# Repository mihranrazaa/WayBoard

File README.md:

# WayBoard
A Keyboard Design for ME and YOU

## Overview
a 60% keyboard design With very minimal design, it is based on RP2040 plus with a type C port which came in-built with the MCU, there total of 61 MX switches design with 5 Stabilizer type switches. A small minimal keyboard :).

## Bit in depth info
The keyboard is designed to be sleek and plane it has RP2040 plus as the MCU and Cherry MX Brown Switches for the keys which are used for versatile purposes (that's what i saw at least). The main firmware is KMK based and the Firmware has already been released, you can find that in the Firmware and Production folder, I hate using different cables so having type c inbuilt in the RP2040 plus is a win-win. I added A small space in the bottom right of the keyboard which will act as a handle kind of things and also look good

---

## Images

**THE ABOVE IMAGES ARE THE LATEST ITERATION OF CAD**

---

## Files to build 

### PCB 

The files for the PCB and Schematics are available in the PCB folder and gerber files are added in the Production folder..

### 3D Case (CAD)

The step files for the keyboard are available in the CAD folder and also in the Production Folder.

Can't add a combine image of pcb with components my laptop can't handle all that together..
Other than this you just have to purchase the Components given below and assemble them.

---

## BOM

| Component                 | Quantity | Note                                                                                    | Price    | Link                                                                                                                                       |
| ------------------------- | -------- | --------------------------------------------------------------------------------------- | -------- | ------------------------------------------------------------------------------------------------------------------------------------------ |
| Cherry MX Switches(Brown) | 1       | Couldn't find a proper retailer on Amazon.They are selling for the right amount i think, | 32USD    | [Available](https://www.keychron.com/products/cherry-switch-set?variant=39298816835673)                                                    |
| White Keycaps set         | 1        | Good Asthetics are important I will keep the body grey :)                               | 25USD    | [Available](https://www.keychron.com/products/cherry-profile-double-shot-pbt-full-set-keycaps-dolch-red-gray-white-mint-blue-black-yellow) |
| Stabilizer set            | 1        | It has 2 extra Stabilizers just in case..                                               | 20USD    | [Available](https://amzn.in/d/dM157FJ) [Available](https://amzn.in/d/5Nto8PQ)                                                              |
| Case & PCB                | 1        | I will make them through any local business                                             | 15-20USD |                                                                                                                                            |
| TOTAL                     |          |                                                                                         | 100USD   |                                                                                                                                            |

Other than this you also need M3 srews but i didn't included them as i already have them..

---

## Extra Stuff

### Gratitude
- Thanks to Hackclub and Hackpad for making me do this brilliant project, More coming :).
- Thanks to my potato for helping me till the end.
- Thanks to myself for completing the project and not getting distracted with another project.
- And Thank you for Reading?

### Challanging
- The only challanging part was designing the PCB and Schematics, first i was overthinking for what MCU should i choose then i took some time on footprints and symbols..
- CAD is TUFF!
---

## End
Check my [BLOG](https://mihranrazaa.pages.dev/)
~ mihranrazaa

BYEEE

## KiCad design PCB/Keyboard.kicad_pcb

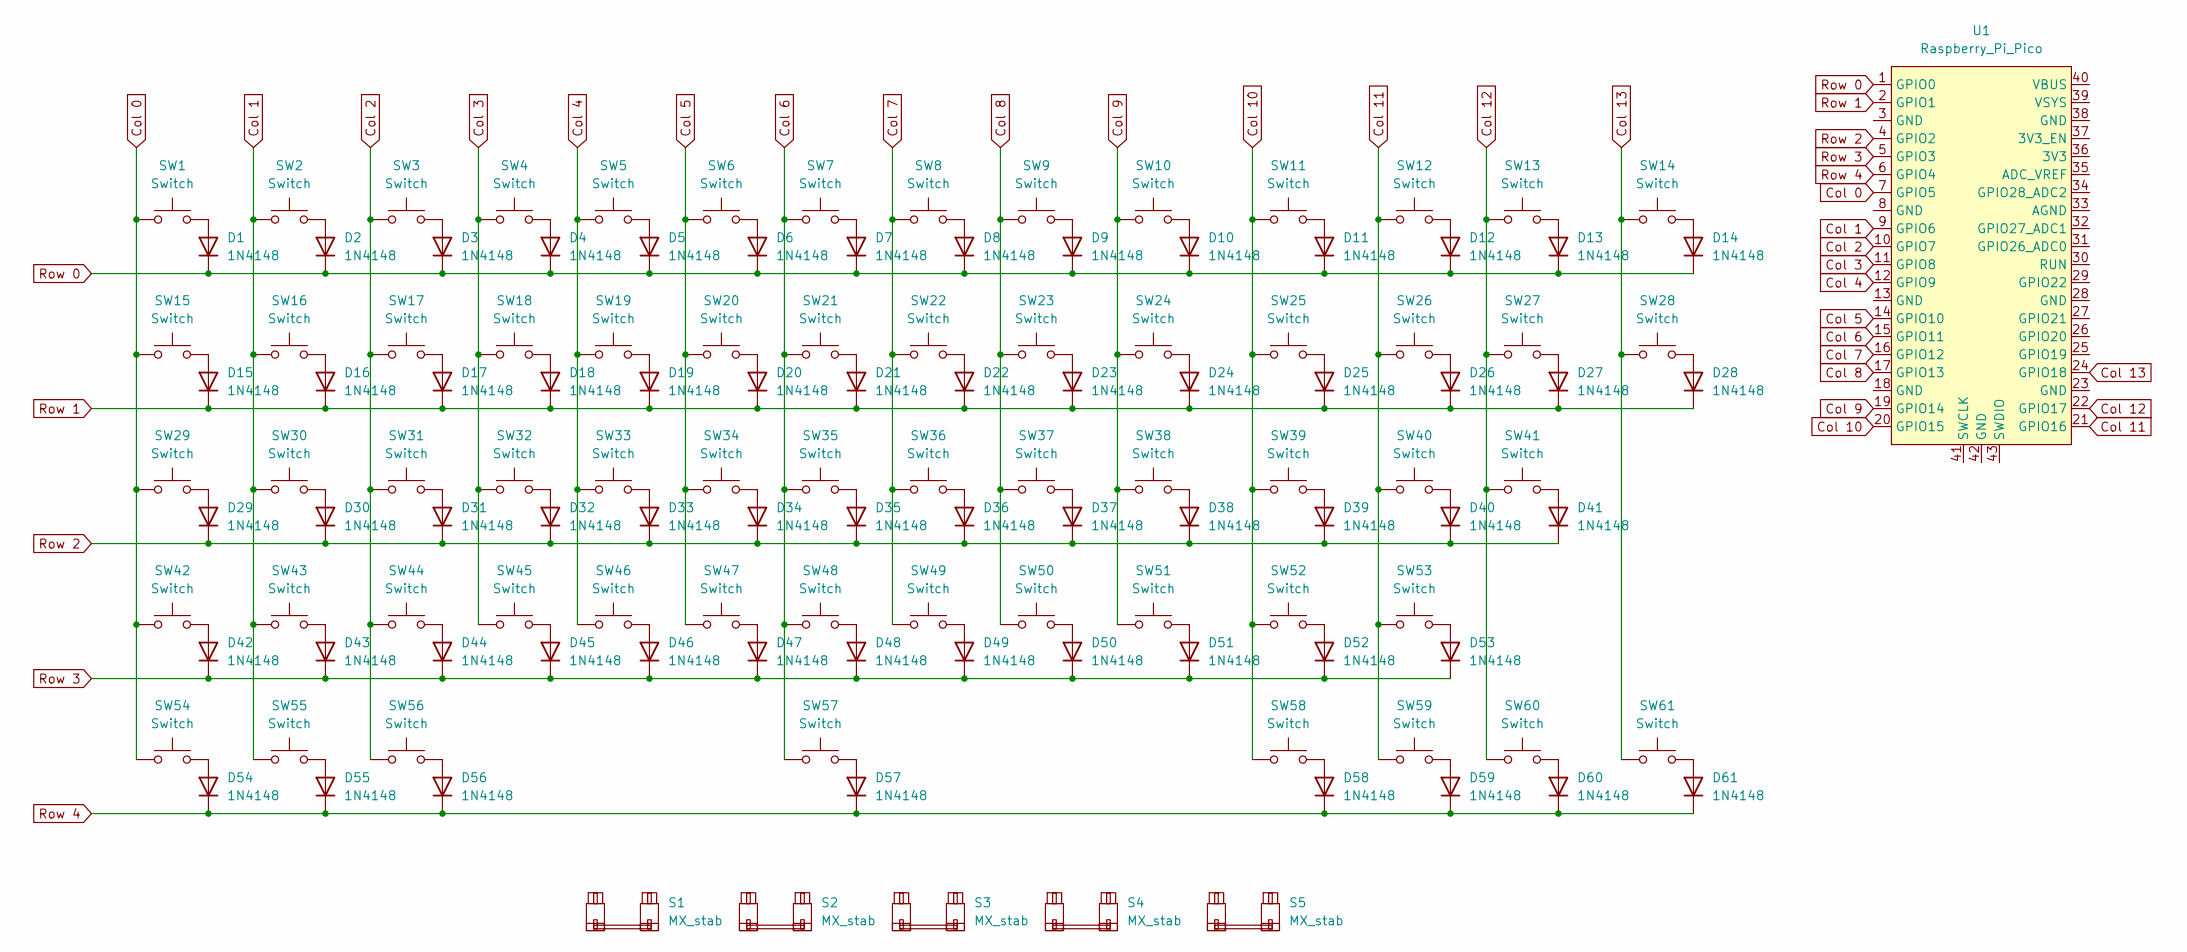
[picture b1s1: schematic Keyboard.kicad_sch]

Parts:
D1, D2, D3, D4, D5, D6, D7, D8, D9, D10, D11, D12, D13, D14, D15, D16, D17, D18, D19, D20, D21, D22, D23, D24, D25, D26, D27, D28, D29, D30, D31, D32, D33, D34, D35, D36, D37, D38, D39, D40, D41, D42, D43, D44, D45, D46, D47, D48, D49, D50, D51, D52, D53, D54, D55, D56, D57, D58, D59, D60, D61: 1N4148; D_DO-35_SOD27_P7.62mm_Horizontal
S1: MX_stab; STAB_MX_P_6.25u
S2: MX_stab; STAB_MX_P_2u
S3, S4: MX_stab; STAB_MX_P_2.25u
S5: MX_stab; STAB_MX_P_2.75u
SW1, SW2, SW3, SW4, SW5, SW6, SW7, SW8, SW9, SW10, SW11, SW12, SW13, SW14, SW16, SW17, SW18, SW19, SW20, SW21, SW22, SW23, SW24, SW25, SW26, SW27, SW30, SW31, SW32, SW33, SW34, SW35, SW36, SW37, SW38, SW39, SW40, SW41, SW42, SW43, SW44, SW45, SW46, SW47, SW48, SW49, SW50, SW51, SW52, SW53, SW57: Switch; SW_MX_1u
SW15, SW28: Switch; SW_MX_1.5u
SW29: Switch; SW_MX_1.75u
SW54, SW55, SW56, SW58, SW59, SW60, SW61: Switch; SW_MX_1.25u
U1: Raspberry_Pi_Pico

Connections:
Col 0: SW1.1, SW15.1, SW29.1, SW42.1, SW54.1, U1.7 (GPIO5)
Col 1: SW2.1, SW16.1, SW30.1, SW43.1, SW55.1, U1.9 (GPIO6)
Col 2: SW3.1, SW17.1, SW31.1, SW44.1, SW56.1, U1.10 (GPIO7)
Col 3: SW4.1, SW18.1, SW32.1, SW45.1, U1.11 (GPIO8)
Col 4: SW5.1, SW19.1, SW33.1, SW46.1, U1.12 (GPIO9)
Col 5: SW6.1, SW20.1, SW34.1, SW47.1, U1.14 (GPIO10)
Col 6: SW7.1, SW21.1, SW35.1, SW48.1, SW57.1, U1.15 (GPIO11)
Col 7: SW8.1, SW22.1, SW36.1, SW49.1, U1.16 (GPIO12)
Col 8: SW9.1, SW23.1, SW37.1, SW50.1, U1.17 (GPIO13)
Col 9: SW10.1, SW24.1, SW38.1, SW51.1, U1.19 (GPIO14)
Col 10: SW11.1, SW25.1, SW39.1, SW52.1, SW58.1, U1.20 (GPIO15)
Col 11: SW12.1, SW26.1, SW40.1, SW53.1, SW59.1, U1.21 (GPIO16)
Col 12: SW13.1, SW27.1, SW41.1, SW60.1, U1.22 (GPIO17)
Col 13: SW14.1, SW28.1, SW61.1, U1.24 (GPIO18)
unnamed: D1.2 (A), SW1.2
unnamed: D2.2 (A), SW2.2
unnamed: D3.2 (A), SW3.2
unnamed: D4.2 (A), SW4.2
unnamed: D5.2 (A), SW5.2
unnamed: D6.2 (A), SW6.2
unnamed: D7.2 (A), SW7.2
unnamed: D8.2 (A), SW8.2
unnamed: D9.2 (A), SW9.2
unnamed: D10.2 (A), SW10.2
unnamed: D11.2 (A), SW11.2
unnamed: D12.2 (A), SW12.2
unnamed: D13.2 (A), SW13.2
unnamed: D14.2 (A), SW14.2
unnamed: D15.2 (A), SW15.2
unnamed: D16.2 (A), SW16.2
unnamed: D17.2 (A), SW17.2
unnamed: D18.2 (A), SW18.2
unnamed: D19.2 (A), SW19.2
unnamed: D20.2 (A), SW20.2
unnamed: D21.2 (A), SW21.2
unnamed: D22.2 (A), SW22.2
unnamed: D23.2 (A), SW23.2
unnamed: D24.2 (A), SW24.2
unnamed: D25.2 (A), SW25.2
unnamed: D26.2 (A), SW26.2
unnamed: D27.2 (A), SW27.2
unnamed: D28.2 (A), SW28.2
unnamed: D29.2 (A), SW29.2
unnamed: D30.2 (A), SW30.2
unnamed: D31.2 (A), SW31.2
unnamed: D32.2 (A), SW32.2
unnamed: D33.2 (A), SW33.2
unnamed: D34.2 (A), SW34.2
unnamed: D35.2 (A), SW35.2
unnamed: D36.2 (A), SW36.2
unnamed: D37.2 (A), SW37.2
unnamed: D38.2 (A), SW38.2
unnamed: D39.2 (A), SW39.2
unnamed: D40.2 (A), SW40.2
unnamed: D41.2 (A), SW41.2
unnamed: D42.2 (A), SW42.2
unnamed: D43.2 (A), SW43.2
unnamed: D44.2 (A), SW44.2
unnamed: D45.2 (A), SW45.2
unnamed: D46.2 (A), SW46.2
unnamed: D47.2 (A), SW47.2
unnamed: D48.2 (A), SW48.2
unnamed: D49.2 (A), SW49.2
unnamed: D50.2 (A), SW50.2
unnamed: D51.2 (A), SW51.2
unnamed: D52.2 (A), SW52.2
unnamed: D53.2 (A), SW53.2
unnamed: D54.2 (A), SW54.2
unnamed: D55.2 (A), SW55.2
unnamed: D56.2 (A), SW56.2
unnamed: D57.2 (A), SW57.2
unnamed: D58.2 (A), SW58.2
unnamed: D59.2 (A), SW59.2
unnamed: D60.2 (A), SW60.2
unnamed: D61.2 (A), SW61.2
Row 0: D1.1 (K), D2.1 (K), D3.1 (K), D4.1 (K), D5.1 (K), D6.1 (K), D7.1 (K), D8.1 (K), D9.1 (K), D10.1 (K), D11.1 (K), D12.1 (K), D13.1 (K), D14.1 (K), U1.1 (GPIO0)
Row 1: D15.1 (K), D16.1 (K), D17.1 (K), D18.1 (K), D19.1 (K), D20.1 (K), D21.1 (K), D22.1 (K), D23.1 (K), D24.1 (K), D25.1 (K), D26.1 (K), D27.1 (K), D28.1 (K), U1.2 (GPIO1)
Row 2: D29.1 (K), D30.1 (K), D31.1 (K), D32.1 (K), D33.1 (K), D34.1 (K), D35.1 (K), D36.1 (K), D37.1 (K), D38.1 (K), D39.1 (K), D40.1 (K), D41.1 (K), U1.4 (GPIO2)
Row 3: D42.1 (K), D43.1 (K), D44.1 (K), D45.1 (K), D46.1 (K), D47.1 (K), D48.1 (K), D49.1 (K), D50.1 (K), D51.1 (K), D52.1 (K), D53.1 (K), U1.5 (GPIO3)
Row 4: D54.1 (K), D55.1 (K), D56.1 (K), D57.1 (K), D58.1 (K), D59.1 (K), D60.1 (K), D61.1 (K), U1.6 (GPIO4)

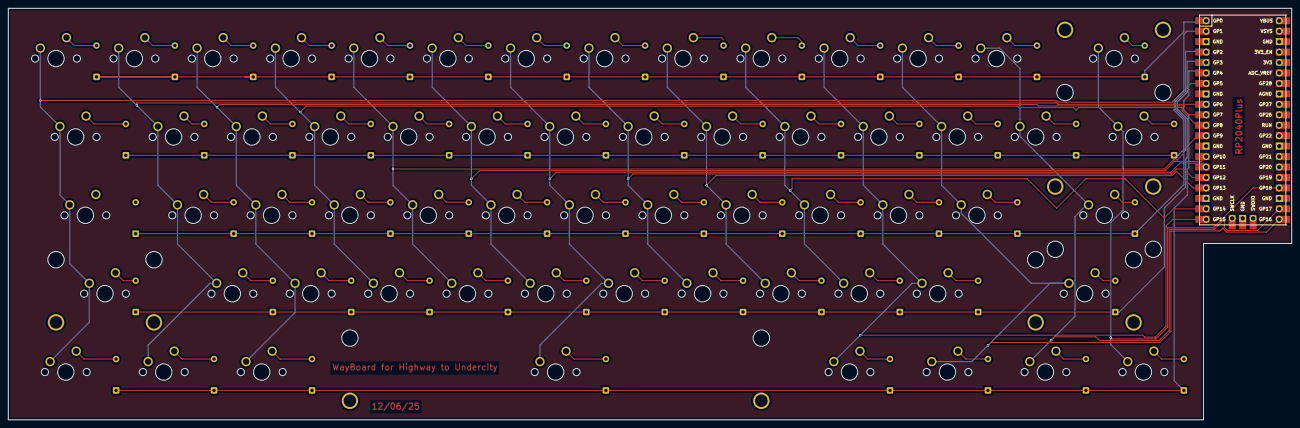
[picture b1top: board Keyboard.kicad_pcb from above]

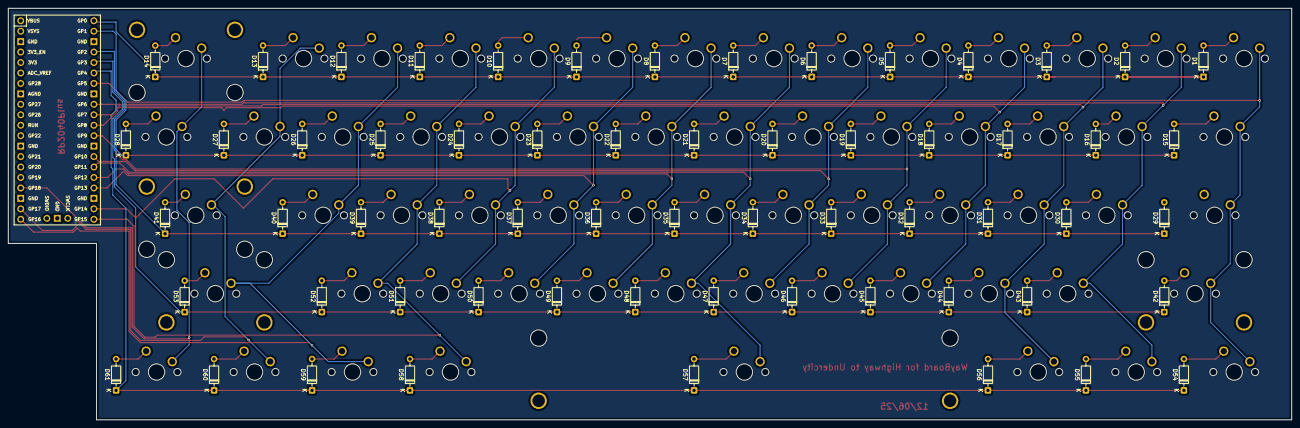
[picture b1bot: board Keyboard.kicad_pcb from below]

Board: 2 copper layers, 311.9 x 100.0 mm, 128 parts (61 on the bottom side), 80 nets.

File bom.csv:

Designator,Footprint,Quantity,Value,LCSC Part #
"D1, D10, D11, D12, D13, D14, D15, D16, D17, D18, D19, D2, D20, D21, D22, D23, D24, D25, D26, D27, D28, D29, D3, D30, D31, D32, D33, D34, D35, D36, D37, D38, D39, D4, D40, D41, D42, D43, D44, D45, D46, D47, D48, D49, D5, D50, D51, D52, D53, D54, D55, D56, D57, D58, D59, D6, D60, D61, D7, D8, D9",D_DO-35_SOD27_P7.62mm_Horizontal,61,1N4148,
S1,STAB_MX_P_6.25u,1,MX_stab,
S2,STAB_MX_P_2u,1,MX_stab,
"S3, S4",STAB_MX_P_2.25u,2,MX_stab,
S5,STAB_MX_P_2.75u,1,MX_stab,
"SW1, SW10, SW11, SW12, SW13, SW14, SW16, SW17, SW18, SW19, SW2, SW20, SW21, SW22, SW23, SW24, SW25, SW26, SW27, SW3, SW30, SW31, SW32, SW33, SW34, SW35, SW36, SW37, SW38, SW39, SW4, SW40, SW41, SW42, SW43, SW44, SW45, SW46, SW47, SW48, SW49, SW5, SW50, SW51, SW52, SW53, SW57, SW6, SW7, SW8, SW9",SW_MX_1u,51,Switch,
"SW15, SW28",SW_MX_1.5u,2,Switch,
SW29,SW_MX_1.75u,1,Switch,
"SW54, SW55, SW56, SW58, SW59, SW60, SW61",SW_MX_1.25u,7,Switch,
U1,Raspberry_Pi_Pico,1,Raspberry_Pi_Pico,

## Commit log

2025-06-14 update journal
2025-06-15 fix photo
2025-06-16 WayboardV1
2025-06-16 update Journal and Readme
2025-06-16 update readme journal body
2025-06-17 fix PCB and add 3d comp
2025-06-23 update cad, readme and journal
2025-07-10 update cad,readme,journal
